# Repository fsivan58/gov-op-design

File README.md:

# gov-op-design
KiCad projects for Govern and Operator boards hardware design.

Both projects were created KiCad 6.0. To open them, it is necessary to add the footprint library footprints/NCP.pretty

### INSTRUCTIONS
1. To add them, go to Preferences -> Manage footrpint libraries. This will open a new window with all the installed footprints.
2. Click the folder icon below the table, go to the footprints/NCP.pretty directory and accept.

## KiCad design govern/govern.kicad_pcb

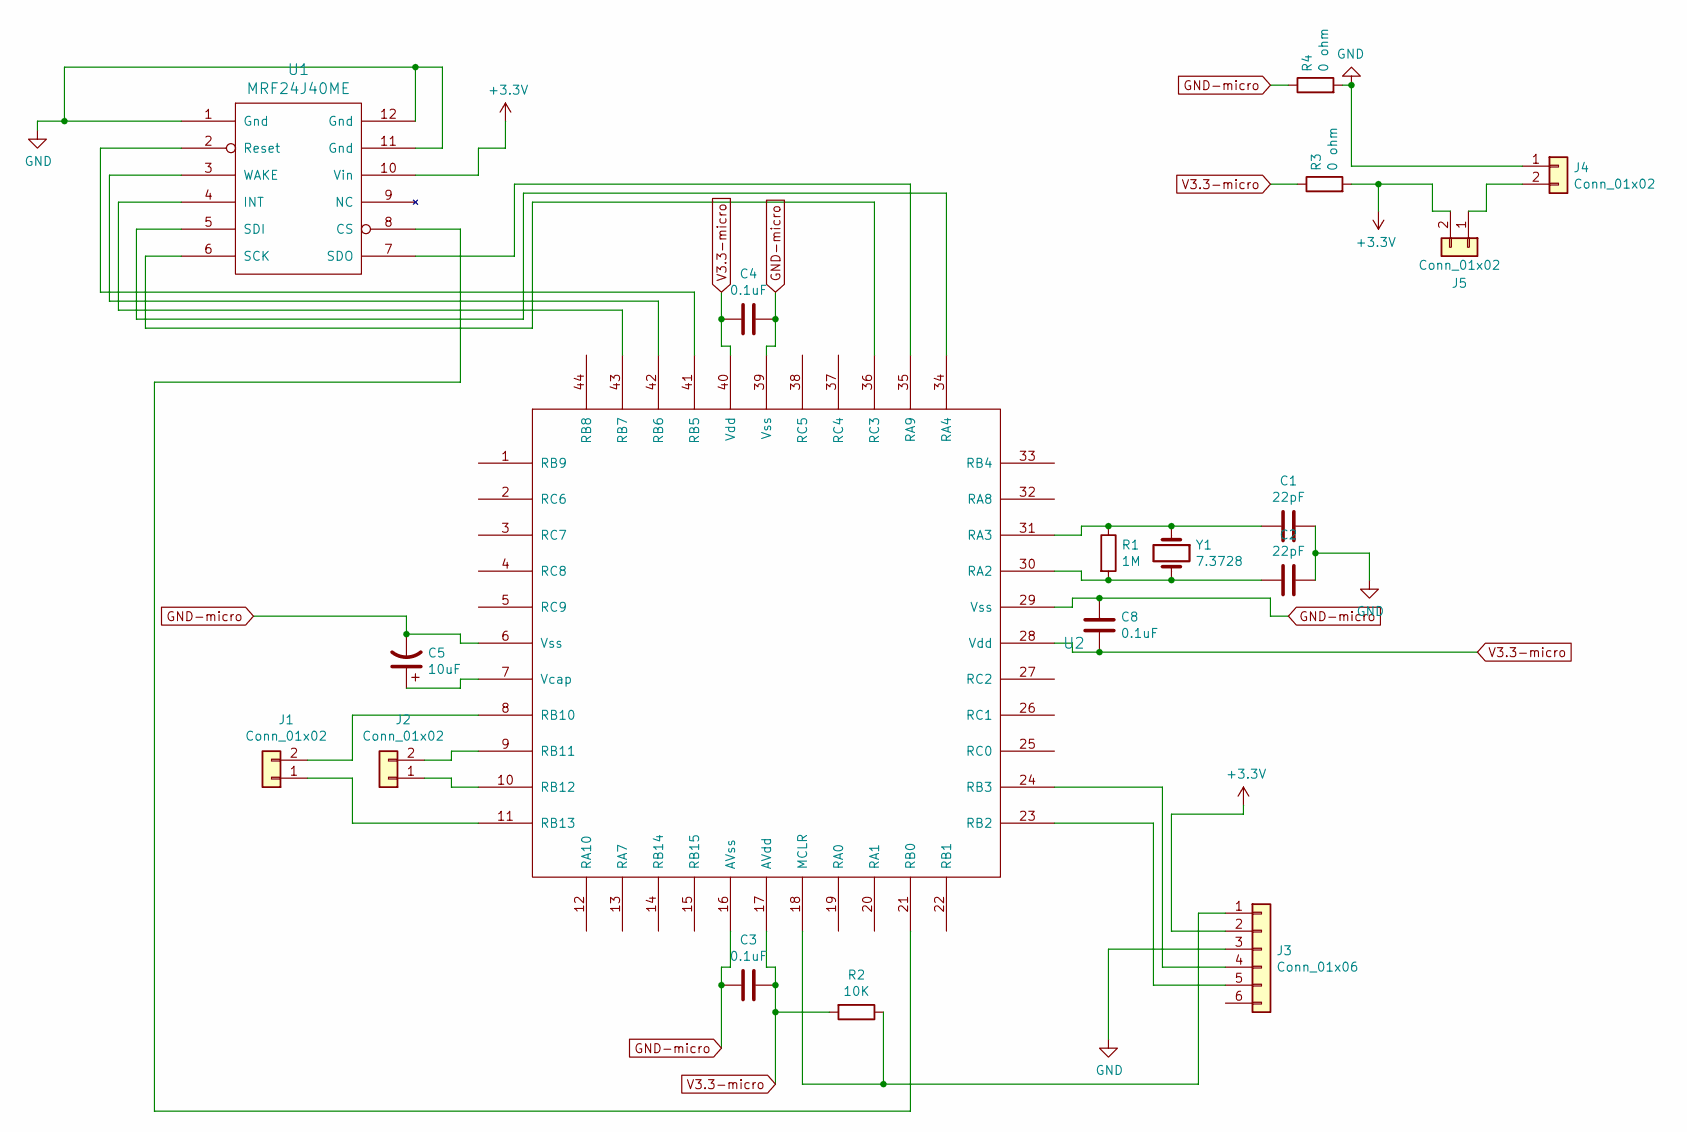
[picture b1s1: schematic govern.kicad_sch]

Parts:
C1, C2: 22pF; C_Rect_L4.0mm_W2.5mm_P2.50mm
C3, C4, C8: 0.1uF; C_Rect_L4.0mm_W2.5mm_P2.50mm
C5: 10uF; CP_Radial_Tantal_D4.5mm_P2.50mm
J1, J2, J5: Conn_01x02; PinHeader_1x02_P2.54mm_Horizontal
J3: Conn_01x06; PinHeader_1x06_P2.54mm_Horizontal
J4: Conn_01x02; TerminalBlock_bornier-2_P5.08mm
R1: 1M; R_Box_L8.4mm_W2.5mm_P5.08mm
R2: 10K; R_Box_L8.4mm_W2.5mm_P5.08mm
R3, R4: 0 ohm; R_Axial_DIN0204_L3.6mm_D1.6mm_P1.90mm_Vertical
U1: MRF24J40ME
U2: DSPIC33EP128GM604; TQFP-44_10x10mm_Pitch0.8mm
Y1: 7.3728; Crystal_HC18-U_Vertical

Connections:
+3V3: J3.2, J5.2, R3.2, U1.10 (Vin)
GND: C1.2, C2.1, J3.3, J4.1, R4.2, U1.1 (Gnd), U1.11 (Gnd), U1.12 (Gnd)
GND-micro: C3.2, C4.1, C5.2, C8.1, R4.1, U2.6 (Vss), U2.16 (AVss), U2.29 (Vss), U2.39 (Vss)
unnamed: C1.1, R1.1, U2.31 (RA3), Y1.1
unnamed: C2.2, R1.2, U2.30 (RA2), Y1.2
unnamed: C5.1, U2.7 (Vcap)
unnamed: J1.1, U2.11 (RB13)
unnamed: J1.2, U2.8 (RB10)
unnamed: J2.1, U2.10 (RB12)
unnamed: J2.2, U2.9 (RB11)
unnamed: J3.1, R2.1, U2.18 (MCLR)
unnamed: J3.4, U2.24 (RB3)
unnamed: J3.5, U2.23 (RB2)
unnamed: J4.2, J5.1
unnamed: U1.2 (Reset), U2.41 (RB5)
unnamed: U1.3 (WAKE), U2.42 (RB6)
unnamed: U1.4 (INT), U2.43 (RB7)
unnamed: U1.5 (SDI), U2.34 (RA4)
unnamed: U1.6 (SCK), U2.36 (RC3)
unnamed: U1.7 (SDO), U2.35 (RA9)
unnamed: U1.8 (CS), U2.21 (RB0)
V3.3-micro: C3.1, C4.2, C8.2, R2.2, R3.1, U2.17 (AVdd), U2.28 (Vdd), U2.40 (Vdd)

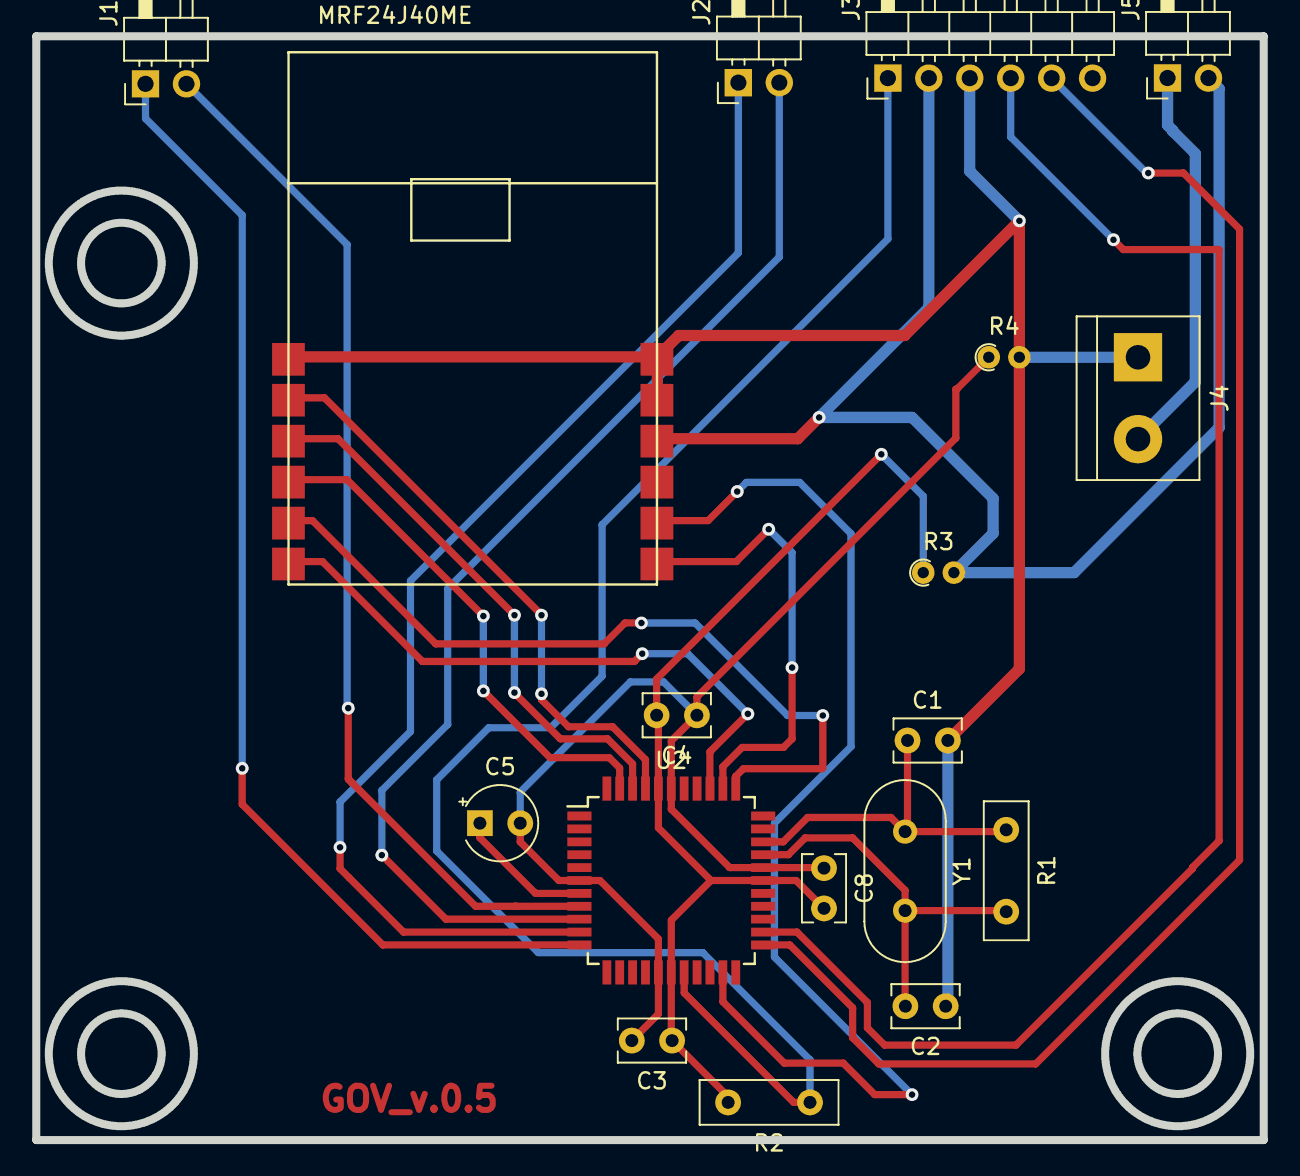
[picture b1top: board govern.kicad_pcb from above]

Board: 2 copper layers, 76.1 x 68.5 mm, 18 parts (0 on the bottom side), 22 nets.

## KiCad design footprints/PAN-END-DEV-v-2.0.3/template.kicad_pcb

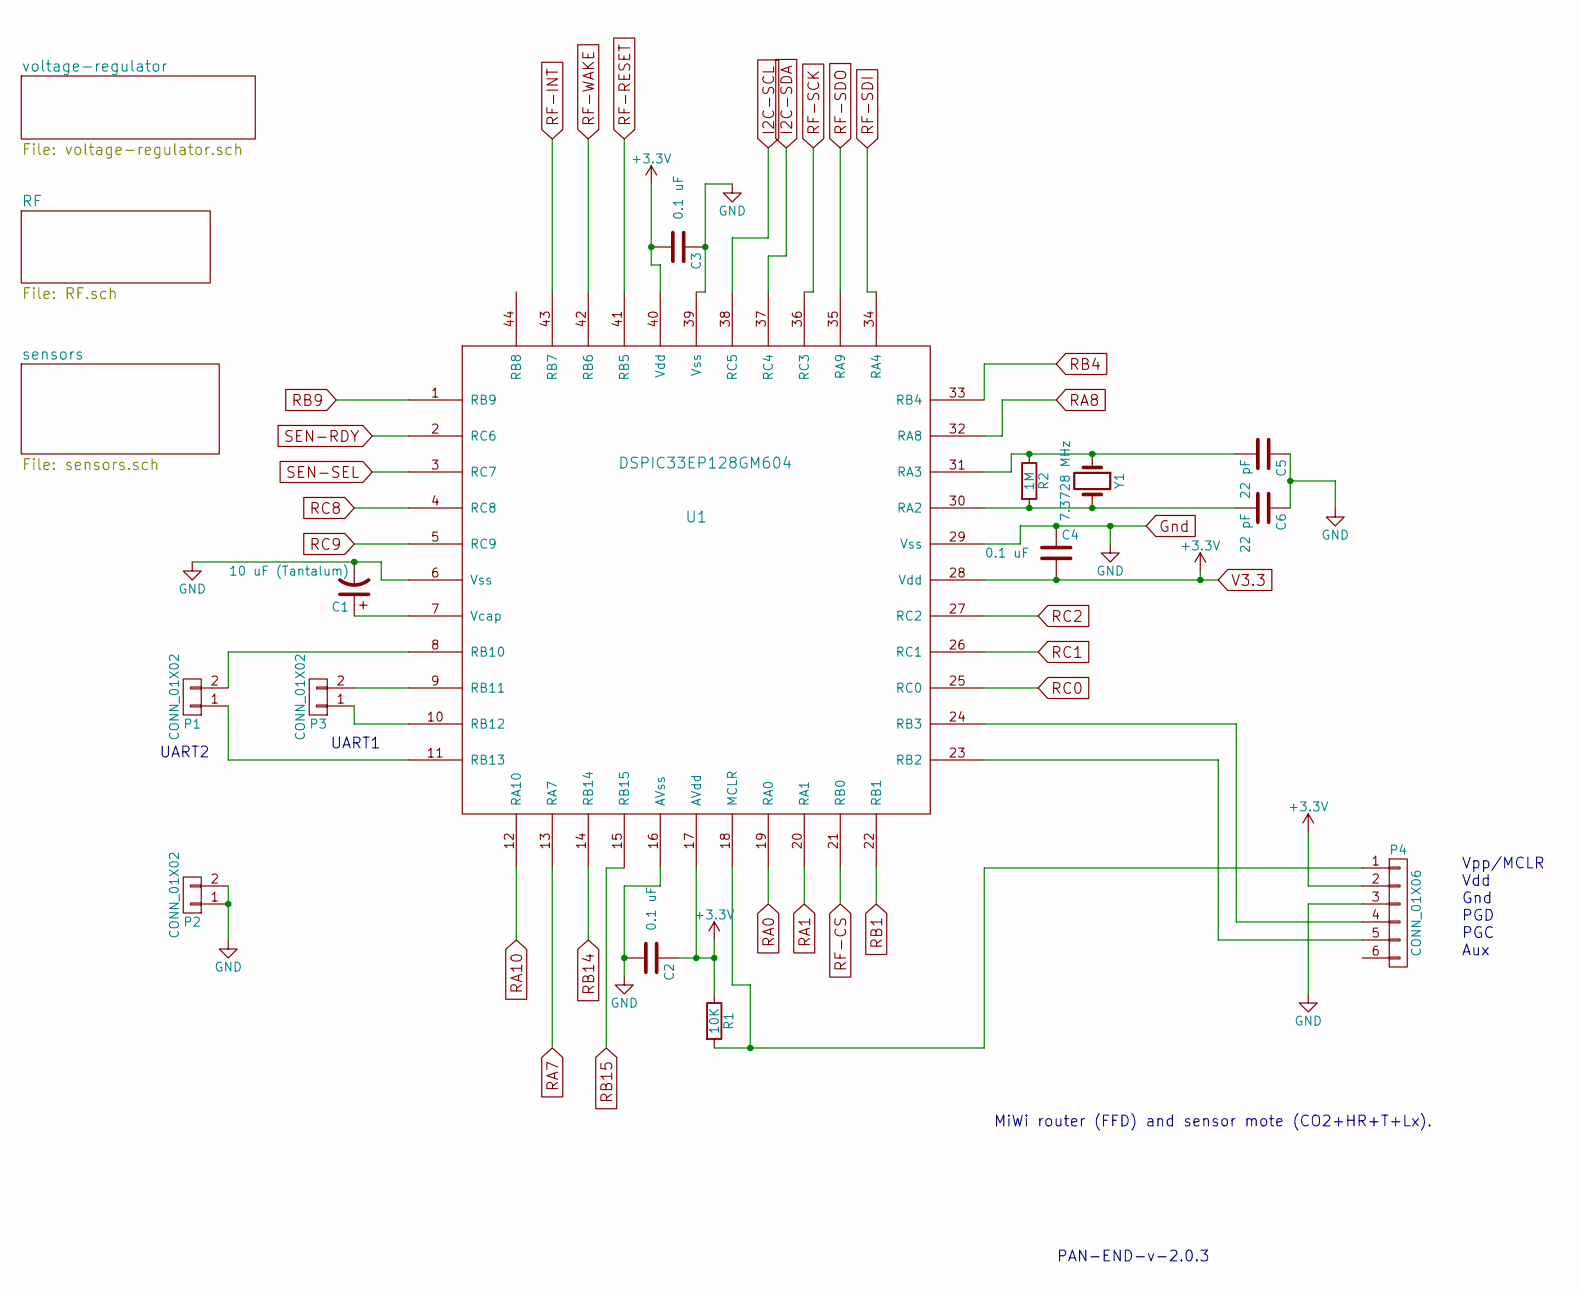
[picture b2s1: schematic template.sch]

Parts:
C1: 10 uF (Tantalum); CP_Radial_Tantal_D4.5mm_P2.50mm
C2, C3, C4: 0.1 uF; C_Rect_L4.0mm_W2.5mm_P2.50mm
C5, C6: 22 pF; C_Rect_L4.0mm_W2.5mm_P2.50mm
P1, P2, P3: CONN_01X02; Pin_Header_Straight_1x02_Pitch2.54mm
P4: CONN_01X06; Pin_Header_Straight_1x06_Pitch2.54mm
R1: 10K; R_Box_L8.4mm_W2.5mm_P5.08mm
R2: 1M; R_Box_L8.4mm_W2.5mm_P5.08mm
U1: DSPIC33EP128GM604; TQFP-44_10x10mm_Pitch0.8mm
Y1: 7.3728 MHz; Crystal_HC18-U_Vertical

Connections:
Gnd: C1.2, C2.2, C3.1, C4.1, C5.1, C6.1, P2.1, P2.2, P4.3, U1.6 (Vss), U1.16 (AVss), U1.29 (Vss), U1.39 (Vss); also elsewhere on the board
I2C-SCL: U1.38 (RC5); also elsewhere on the board
I2C-SDA: U1.37 (RC4); also elsewhere on the board
unnamed: C1.1, U1.7 (Vcap)
unnamed: C5.2, R2.1, U1.31 (RA3), Y1.1
unnamed: C6.2, R2.2, U1.30 (RA2), Y1.2
unnamed: P1.1, U1.11 (RB13)
unnamed: P1.2, U1.8 (RB10)
unnamed: P3.1, U1.10 (RB12)
unnamed: P3.2, U1.9 (RB11)
unnamed: P4.1, R1.2, U1.18 (MCLR)
unnamed: P4.4, U1.24 (RB3)
unnamed: P4.5, U1.23 (RB2)
RA0: U1.19 (RA0)
RA1: U1.20 (RA1)
RA7: U1.13 (RA7)
RA8: U1.32 (RA8)
RA10: U1.12 (RA10)
RB1: U1.22 (RB1)
RB4: U1.33 (RB4)
RB9: U1.1 (RB9)
RB14: U1.14 (RB14)
RB15: U1.15 (RB15)
RC0: U1.25 (RC0)
RC1: U1.26 (RC1)
RC2: U1.27 (RC2)
RC8: U1.4 (RC8)
RC9: U1.5 (RC9)
RF-CS: U1.21 (RB0); also elsewhere on the board
RF-INT: U1.43 (RB7); also elsewhere on the board
RF-RESET: U1.41 (RB5); also elsewhere on the board
RF-SCK: U1.36 (RC3); also elsewhere on the board
RF-SDI: U1.34 (RA4); also elsewhere on the board
RF-SDO: U1.35 (RA9); also elsewhere on the board
RF-WAKE: U1.42 (RB6); also elsewhere on the board
SEN-RDY: U1.2 (RC6); also elsewhere on the board
SEN-SEL: U1.3 (RC7); also elsewhere on the board
V3.3: C2.1, C3.2, C4.2, P4.2, R1.1, U1.17 (AVdd), U1.28 (Vdd), U1.40 (Vdd); also elsewhere on the board

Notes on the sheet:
UART1
UART2
Vpp/MCLR Vdd Gnd PGD PGC Aux
MiWi router (FFD) and sensor mote (CO2+HR+T+Lx).
PAN-END-v-2.0.3

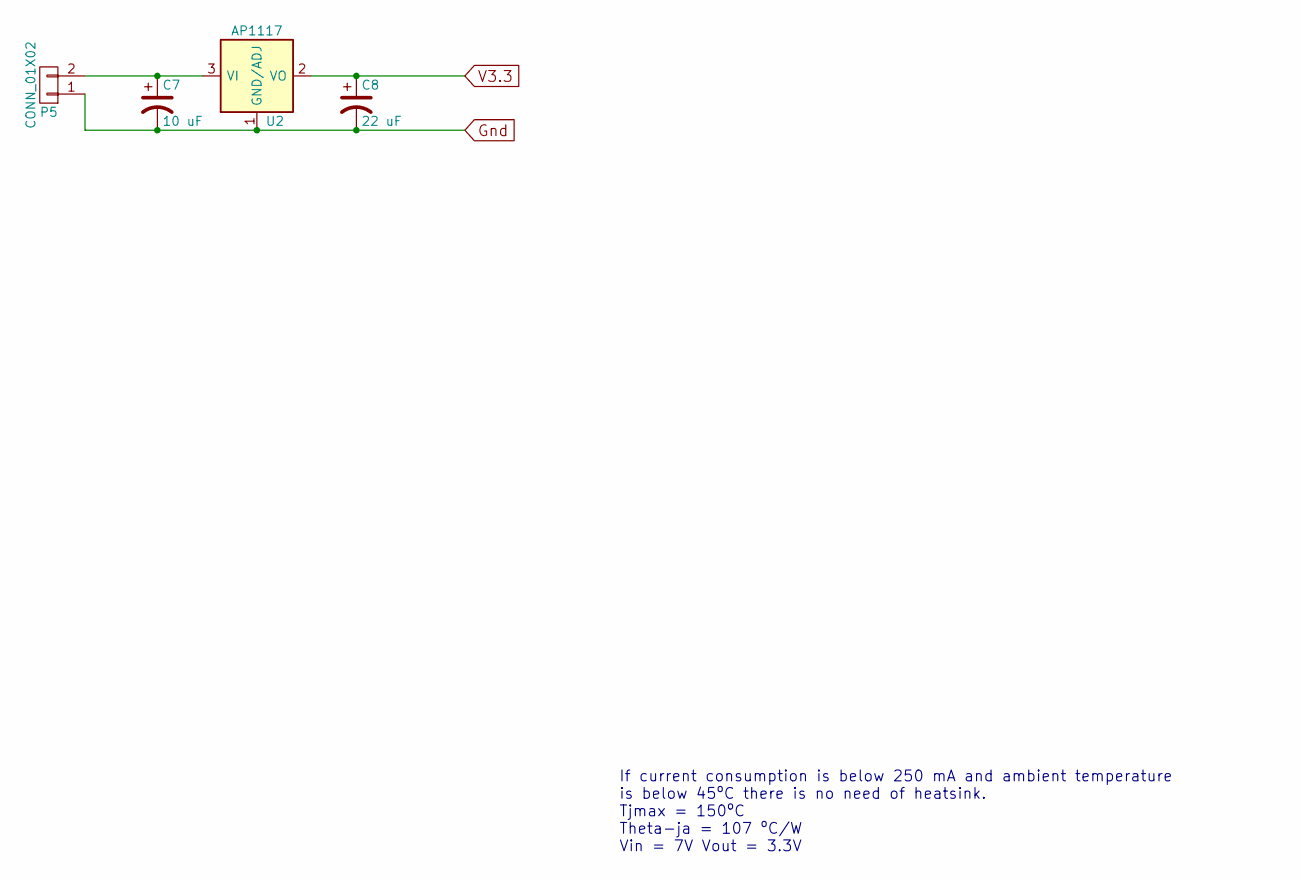
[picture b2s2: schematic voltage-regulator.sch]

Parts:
C7: 10 uF; C_Rect_L4.0mm_W2.5mm_P2.50mm
C8: 22 uF; C_Rect_L4.0mm_W2.5mm_P2.50mm
P5: CONN_01X02; bornier2
U2: AP1117; SOT-223

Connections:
Gnd: C7.2, C8.2, P5.1, U2.1 (GND/ADJ); also elsewhere on the board
unnamed: C7.1, P5.2, U2.3 (VI)
V3.3: C8.1, U2.2 (VO), U2.4 (VO); also elsewhere on the board

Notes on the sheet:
If current consumption is below 250 mA and ambient temperature is below 45ºC there is no need of heatsink. Tjmax = 150ºC Theta-ja = 107 ºC/W Vin = 7V Vout = 3.3V

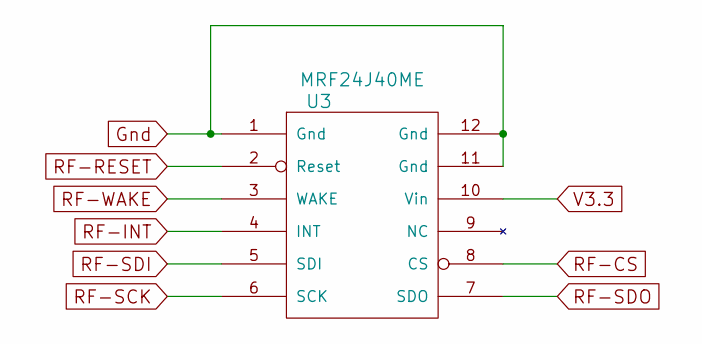
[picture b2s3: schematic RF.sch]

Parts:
U3: MRF24J40ME

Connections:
Gnd: U3.1 (Gnd), U3.11 (Gnd), U3.12 (Gnd); also elsewhere on the board
RF-CS: U3.8 (CS); also elsewhere on the board
RF-INT: U3.4 (INT); also elsewhere on the board
RF-RESET: U3.2 (Reset); also elsewhere on the board
RF-SCK: U3.6 (SCK); also elsewhere on the board
RF-SDI: U3.5 (SDI); also elsewhere on the board
RF-SDO: U3.7 (SDO); also elsewhere on the board
RF-WAKE: U3.3 (WAKE); also elsewhere on the board
V3.3: U3.10 (Vin); also elsewhere on the board

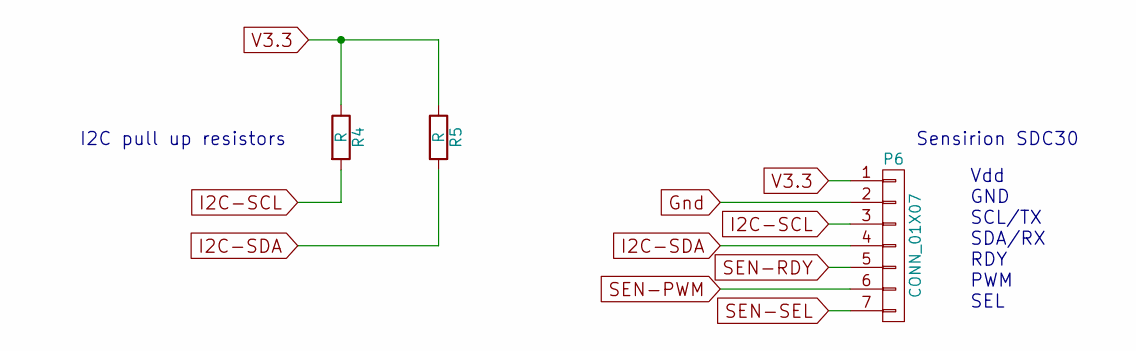
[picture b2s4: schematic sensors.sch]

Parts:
P6: CONN_01X07; Pin_Header_Straight_1x07_Pitch2.54mm
R4, R5: R; R_Box_L8.4mm_W2.5mm_P5.08mm

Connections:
Gnd: P6.2; also elsewhere on the board
I2C-SCL: P6.3, R4.2; also elsewhere on the board
I2C-SDA: P6.4, R5.2; also elsewhere on the board
SEN-PWM: P6.6
SEN-RDY: P6.5; also elsewhere on the board
SEN-SEL: P6.7; also elsewhere on the board
V3.3: P6.1, R4.1, R5.1; also elsewhere on the board

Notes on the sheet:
Vdd GND SCL/TX SDA/RX RDY PWM SEL
Sensirion SDC30
I2C pull up resistors

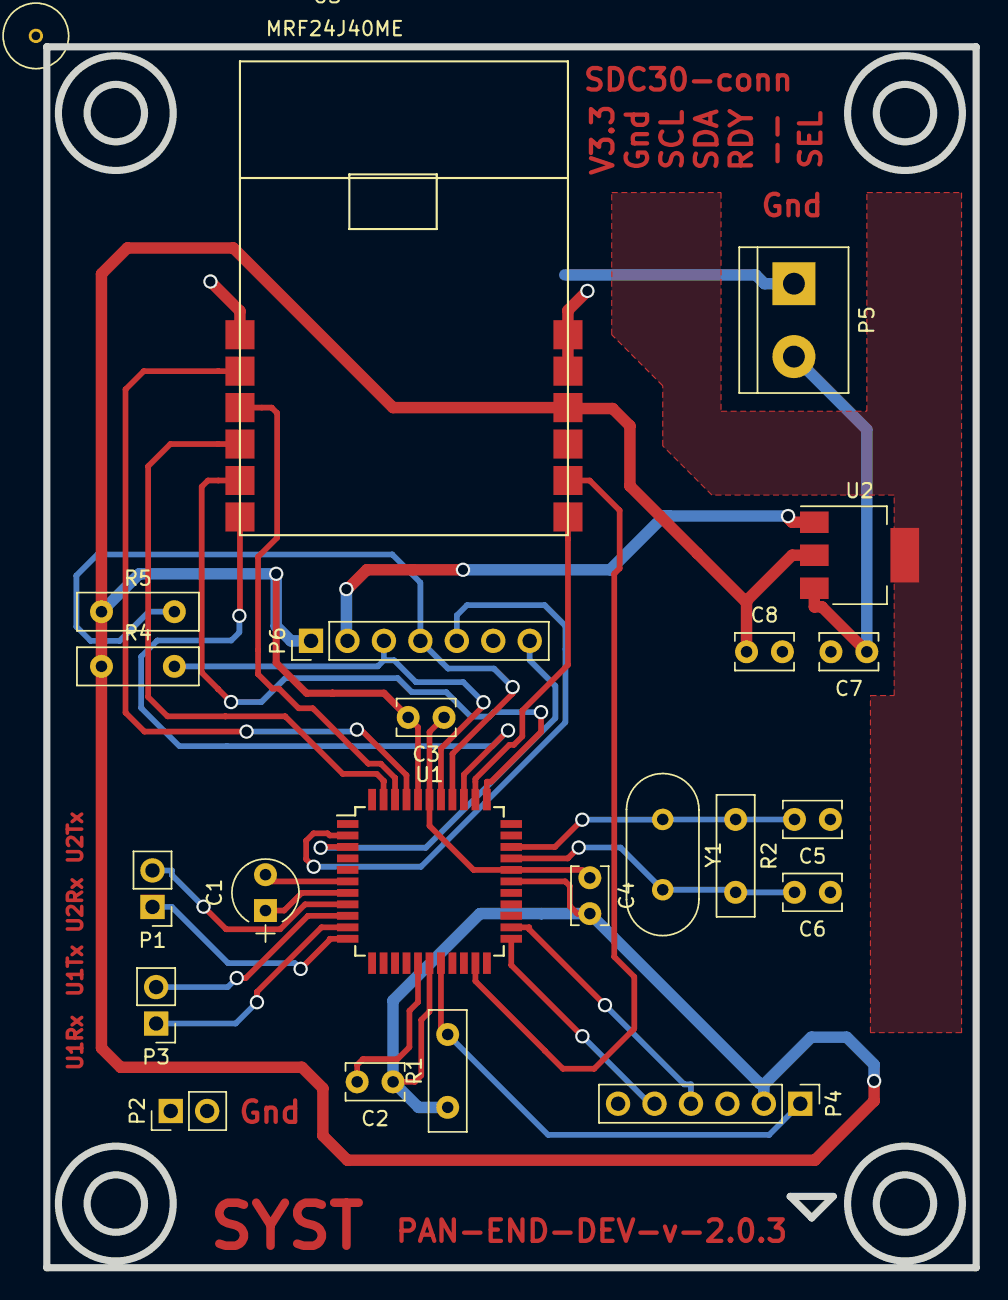
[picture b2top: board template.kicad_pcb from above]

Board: 2 copper layers, 64.8 x 85.1 mm, 22 parts (0 on the bottom side), 24 nets.

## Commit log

2023-01-21 Added README.md
2023-01-21 Added Govern project
2023-01-21 Added Operator project
2023-01-21 Added footprints
2023-01-21 Added gitignore
2023-01-28 updated footprints
2023-01-28 OP v.0.5
2023-01-28 deleted backups
2023-01-28 GOV v.0.5
2023-03-18 ps files
